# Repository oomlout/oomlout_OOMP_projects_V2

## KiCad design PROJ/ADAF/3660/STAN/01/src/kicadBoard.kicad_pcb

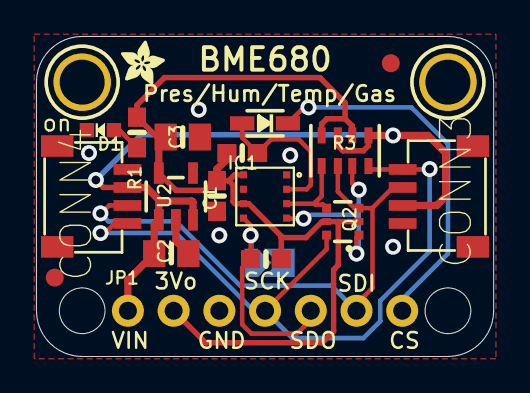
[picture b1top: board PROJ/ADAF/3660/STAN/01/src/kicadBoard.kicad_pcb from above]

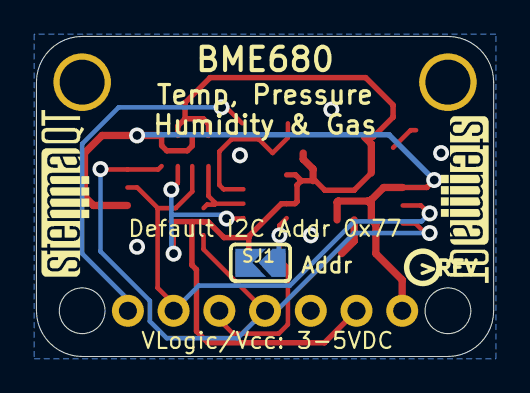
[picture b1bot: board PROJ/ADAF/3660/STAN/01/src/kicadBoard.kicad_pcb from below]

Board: 2 copper layers, 25.4 x 17.8 mm, 26 parts (4 on the bottom side), 11 nets.

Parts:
@HOLE0, @HOLE1: (no value)
C1: 0.1uF; 0603-NO
C2, C3: 10uF; 0805-NO
CONN3, CONN4: STEMMA_I2C_QT; JST_SH4
D1: GREEN; CHIPLED_0603_NOOUTLINE
D2: 1N4148; SOD-323
FID3, FID4: FIDUCIAL_1MM
IC1: BME680
JP1: 1X07_ROUND_70
Q2: BSS138; SOT363
R1, R4, R5: 10K; 0603-NO
R3: 10K; RESPACK_4X0603
SJ1: SOLDERJUMPER_ARROW_NOPASTE
U2: AP2112K-3.3; SOT23-5
U$1, U$17: MOUNTINGHOLE2.5; MOUNTINGHOLE_2.5_PLATED
U$4: ADAFRUIT_2.5MM
U$25: PCBFEAT-REV-040
U$30, U$31: STEMMAQT

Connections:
3.3V: C1.1, C3.1, IC1.6, IC1.8, JP1.2, Q2.2, Q2.5, R1.1, R3.2, R3.4, R4.2, R5.2, U2.5
CS: D2.C, JP1.7
CS_3V: D2.A, IC1.2, R5.1
GND: C1.2, C2.2, C3.2, CONN3.1, CONN4.1, D1.C, IC1.1, IC1.7, JP1.3, SJ1.2, U2.2
unnamed: D1.A, R1.2
SCK/SCL: CONN3.4, CONN4.4, JP1.4, Q2.6, R3.8
SCK_3V: IC1.4, Q2.1, R3.7
SDI/SDA: CONN3.3, CONN4.3, JP1.6, Q2.3, R3.6
SDI_3V: IC1.3, Q2.4, R3.5
SDO/ADR: IC1.5, JP1.5, R4.1, SJ1.1
VCC: C2.1, CONN3.2, CONN4.2, JP1.1, R3.1, R3.3, U2.1, U2.3

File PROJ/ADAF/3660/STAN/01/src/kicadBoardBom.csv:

"Id";"Designator";"Package";"Quantity";"Designation";"Supplier and ref";
1;"R5,R1,R4";"0603-NO";3;"10K";;;
2;"@HOLE1,@HOLE0";"";2;"";;;
3;"U$1,U$17";"MOUNTINGHOLE_2.5_PLATED";2;"MOUNTINGHOLE2.5";;;
4;"C2,C3";"0805-NO";2;"10uF";;;
5;"Q2";"SOT363";1;"BSS138";;;
6;"R3";"RESPACK_4X0603";1;"10K";;;
7;"C1";"0603-NO";1;"0.1uF";;;
8;"U2";"SOT23-5";1;"AP2112K-3.3";;;
9;"D1";"CHIPLED_0603_NOOUTLINE";1;"GREEN";;;
10;"U$4";"ADAFRUIT_2.5MM";1;"";;;
11;"CONN3,CONN4";"JST_SH4";2;"STEMMA_I2C_QT";;;
12;"D2";"SOD-323";1;"1N4148";;;
13;"IC1";"BME680";1;"BME680";;;
14;"JP1";"1X07_ROUND_70";1;"";;;
15;"FID3,FID4";"FIDUCIAL_1MM";2;"FIDUCIAL_1MM";;;
16;"U$25";"PCBFEAT-REV-040";1;"";;;
17;"U$31,U$30";"STEMMAQT";2;"";;;
18;"SJ1";"SOLDERJUMPER_ARROW_NOPASTE";1;"";;;

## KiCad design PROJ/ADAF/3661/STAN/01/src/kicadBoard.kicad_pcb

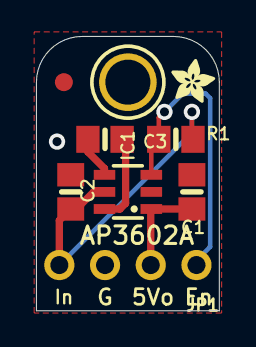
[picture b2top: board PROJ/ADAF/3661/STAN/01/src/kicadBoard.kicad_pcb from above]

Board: 2 copper layers, 10.2 x 15.2 mm, 10 parts (1 on the bottom side), 6 nets.

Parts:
C1, C2: 10uF; 0805-NO
C3: 1uF; 0805-NO
FID1: FIDUCIAL""; FIDUCIAL_1MM
IC1: AP3602; SOT23-6
JP1: 1X04_ROUND
R1: 100K; 0805-NO
U$9: MOUNTINGHOLE2.5; MOUNTINGHOLE_2.5_PLATED
U$10: PCBFEAT-REV-040
U$11: ADAFRUIT_2.5MM

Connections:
5.0V: C1.1, IC1.1, JP1.2
GND: C1.2, C2.2, IC1.2, JP1.3
unnamed: C3.2, IC1.6
unnamed: C3.1, IC1.4
VIN: C2.1, IC1.5, JP1.4, R1.1
~SHDN: IC1.3, JP1.1, R1.2

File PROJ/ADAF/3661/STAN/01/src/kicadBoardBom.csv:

"Id";"Designator";"Package";"Quantity";"Designation";"Supplier and ref";
1;"C2,C1";"0805-NO";2;"10uF";;;
2;"FID1";"FIDUCIAL_1MM";1;"FIDUCIAL""";;;
3;"U$11";"ADAFRUIT_2.5MM";1;"";;;
4;"U$9";"MOUNTINGHOLE_2.5_PLATED";1;"MOUNTINGHOLE2.5";;;
5;"JP1";"1X04_ROUND";1;"";;;
6;"R1";"0805-NO";1;"100K";;;
7;"IC1";"SOT23-6";1;"AP3602";;;
8;"C3";"0805-NO";1;"1uF";;;
9;"U$10";"PCBFEAT-REV-040";1;"";;;

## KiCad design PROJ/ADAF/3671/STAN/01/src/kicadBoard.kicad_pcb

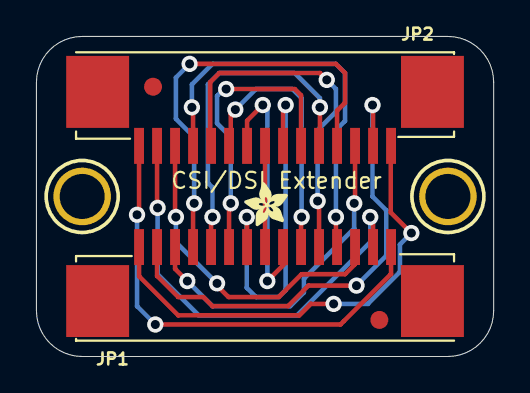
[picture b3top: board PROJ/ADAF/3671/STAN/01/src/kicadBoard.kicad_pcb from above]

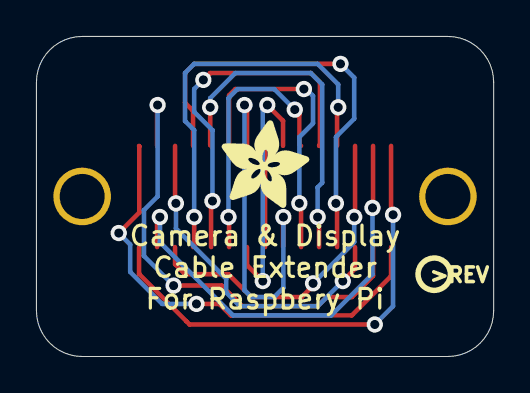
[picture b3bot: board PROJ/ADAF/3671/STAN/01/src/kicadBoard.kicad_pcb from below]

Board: 2 copper layers, 25.4 x 17.8 mm, 9 parts (2 on the bottom side), 15 nets.

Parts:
FID1, FID2: FIDUCIAL_1MM
JP1, JP2: FPC_15PIN_1.0MM
U$2, U$3: MOUNTINGHOLE2.5; MOUNTINGHOLE_2.5_PLATED
U$4: ADAFRUIT_2.5MM
U$5: ADAFRUIT_5MM
U$6: PCBFEAT-REV-040

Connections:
unnamed: JP1.1, JP2.1
unnamed: JP1.2, JP2.2
unnamed: JP1.3, JP2.3
unnamed: JP1.4, JP2.4
unnamed: JP1.5, JP2.5
unnamed: JP1.6, JP2.6
unnamed: JP1.7, JP2.7
unnamed: JP1.8, JP2.8
unnamed: JP1.9, JP2.9
unnamed: JP1.10, JP2.10
unnamed: JP1.11, JP2.11
unnamed: JP1.12, JP2.12
unnamed: JP1.13, JP2.13
unnamed: JP1.14, JP2.14
unnamed: JP1.15, JP2.15

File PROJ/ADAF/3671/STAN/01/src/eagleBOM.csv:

"Part";"Value";"Device";"Package";"Description";"BOM";
"FID1";"FIDUCIAL_1MM";"FIDUCIAL_1MM";"FIDUCIAL_1MM";"Fiducial Alignment Points";"EXCLUDE";
"FID2";"FIDUCIAL_1MM";"FIDUCIAL_1MM";"FIDUCIAL_1MM";"Fiducial Alignment Points";"EXCLUDE";
"JP1";"";"HEADER-1X15_FPC1MM_PI";"FPC_15PIN_1.0MM";"1x15 Header";"";
"JP2";"";"HEADER-1X15_FPC1MM_PI";"FPC_15PIN_1.0MM";"1x15 Header";"";
"U$2";"MOUNTINGHOLE2.5";"MOUNTINGHOLE2.5";"MOUNTINGHOLE_2.5_PLATED";"Mounting Hole";"EXCLUDE";
"U$3";"MOUNTINGHOLE2.5";"MOUNTINGHOLE2.5";"MOUNTINGHOLE_2.5_PLATED";"Mounting Hole";"EXCLUDE";

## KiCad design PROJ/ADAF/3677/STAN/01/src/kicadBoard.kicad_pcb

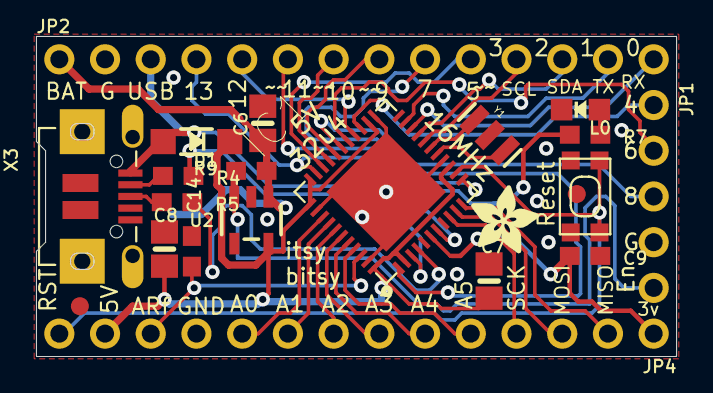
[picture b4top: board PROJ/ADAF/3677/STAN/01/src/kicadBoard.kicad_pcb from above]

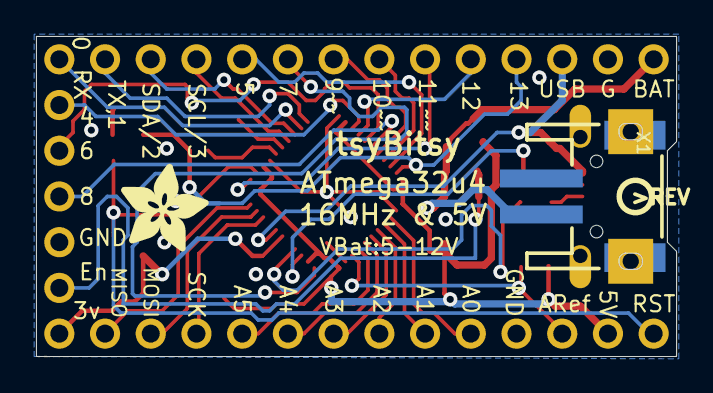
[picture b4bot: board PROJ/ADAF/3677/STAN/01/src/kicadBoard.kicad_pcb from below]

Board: 2 copper layers, 35.6 x 17.8 mm, 25 parts (3 on the bottom side), 38 nets.

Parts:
C6, C8: 10µF; 0805-NO
C7: 10uF; 0805-NO
C9, C14: 1uF; 0603-NO
D1: MBR120; SOD-123
IC1: ATMEGA32U4-MU; TQFN44_7MM
JP1: 1X05_ROUND
JP2, JP4: 1X14_ROUND70
L0: RED; CHIPLED_0805_NOOUTLINE
R4, R5: 22; 0603-NO
R7: 2.2K; 0603-NO
R9: 100k; 0603-NO
SW1: SPST_TACT-KMR2; KMR2
U2: MIC5225-5.0; SOT23-5
U$4: ADAFRUIT_5MM
U$7: ADAFRUIT_3.5MM
U$10: PCBFEAT-REV-040
U$34, U$35: FIDUCIAL""; FIDUCIAL_1MM
X1: JSTPH2
X3: microUSB; 4UCONN_20329_V2
Y1: 16MHz; RESONATOR-SMD

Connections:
3.3V: C9.1, IC1.6, JP4.1
+5V: C7.1, C8.1, D1.C, IC1.2, IC1.14, IC1.24, IC1.33, IC1.34, IC1.44, JP4.13, U2.5
A0: IC1.36, JP4.10
A1: IC1.37, JP4.9
A2: IC1.38, JP4.8
A3: IC1.39, JP4.7
A4: IC1.40, JP4.6
A5: IC1.41, JP4.5
AREF: C14.1, IC1.42, JP4.12
D0: IC1.20, JP2.14
D1: IC1.21, JP2.13
D4: IC1.25, JP1.1
D5: IC1.31, JP2.10
D6: IC1.27, JP1.2
D7: IC1.1, JP2.9
D8: IC1.28, JP1.3
D9: IC1.29, JP2.8
D10: IC1.30, JP2.7
D11: IC1.12, JP2.6
D12: IC1.26, JP2.5
D13: IC1.32, JP2.4, R7.1
D+: IC1.4, R5.2
D-: IC1.3, R4.2
EN: JP1.5, R9.2, U2.3
GND: C6.2, C7.2, C8.2, C9.2, C14.2, IC1.5, IC1.15, IC1.23, IC1.35, IC1.43, JP1.4, JP2.2, JP4.11, L0.C, SW1.2, SW1.4, U2.2, X1.1, X3.BASE@1, X3.BASE@2, X3.GND, X3.SPRT@1, X3.SPRT@2, X3.SPRT@3, X3.SPRT@4, Y1.2
MISO: IC1.11, JP4.2
MOSI: IC1.10, JP4.3
unnamed: L0.A, R7.2
unnamed: IC1.16, Y1.3
unnamed: IC1.17, Y1.1
unnamed: R5.1, X3.D+
unnamed: R4.1, X3.D-
RST: IC1.13, JP4.14, SW1.1, SW1.3
SCK: IC1.9, JP4.4
SCL: IC1.18, JP2.11
SDA: IC1.19, JP2.12
VBAT: C6.1, JP2.1, R9.1, U2.1, X1.2
VBUS: D1.A, IC1.7, JP2.3, X3.VBUS

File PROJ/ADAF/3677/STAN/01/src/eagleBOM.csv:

"Part";"Value";"Device";"Package";"Description";"BOM";
"C6";"10µF";"CAP_CERAMIC0805-NOOUTLINE";"0805-NO";"Ceramic Capacitors";"";
"C7";"10uF";"CAP_CERAMIC0805-NOOUTLINE";"0805-NO";"Ceramic Capacitors";"";
"C8";"10µF";"CAP_CERAMIC0805-NOOUTLINE";"0805-NO";"Ceramic Capacitors";"";
"C9";"1uF";"CAP_CERAMIC0603_NO";"0603-NO";"Ceramic Capacitors";"";
"C14";"1uF";"CAP_CERAMIC0603_NO";"0603-NO";"Ceramic Capacitors";"";
"D1";"MBR120";"DIODE-SCHOTTKYSOD-123";"SOD-123";"";"";
"IC1";"ATMEGA32U4-MU";"ATMEGA32U4-MU";"TQFN44_7MM";"http://www.ladyada.net/library/eagle";"";
"JP1";"";"HEADER-1X5ROUND";"1X05_ROUND";"PIN HEADER";"";
"JP2";"";"HEADER-1X14";"1X14_ROUND70";"";"";
"JP4";"";"HEADER-1X14";"1X14_ROUND70";"";"";
"L";"RED";"LED0805_NOOUTLINE";"CHIPLED_0805_NOOUTLINE";"LED";"";
"R4";"22";"RESISTOR_0603_NOOUT";"0603-NO";"Resistors";"";
"R5";"22";"RESISTOR_0603_NOOUT";"0603-NO";"Resistors";"";
"R7";"2.2K";"RESISTOR_0603_NOOUT";"0603-NO";"Resistors";"";
"R9";"100k";"RESISTOR_0603_NOOUT";"0603-NO";"Resistors";"";
"SW1";"SPST_TACT-KMR2";"SPST_TACT-KMR2";"KMR2";"SMT 6mm switch, EVQQ2 series";"";
"U$34";"FIDUCIAL""";"FIDUCIAL""";"FIDUCIAL_1MM";"Fiducial Alignment Points";"EXCLUDE";
"U$35";"FIDUCIAL""";"FIDUCIAL""";"FIDUCIAL_1MM";"Fiducial Alignment Points";"EXCLUDE";
"U2";"MIC5225-5.0";"VREG_SOT23-5";"SOT23-5";"SOT23-5 Fixed Voltage Regulators";"";
"X1";"";"CON_JST_PH_2PIN";"JSTPH2";"JST 2-Pin Right-Angle Connector";"";
"X3";"microUSB";"USB_MICRO_20329_V2";"4UCONN_20329_V2";"USB Connectors";"";
"Y1";"16MHz";"RESONATORSMD";"RESONATOR-SMD";"Resonator";"";

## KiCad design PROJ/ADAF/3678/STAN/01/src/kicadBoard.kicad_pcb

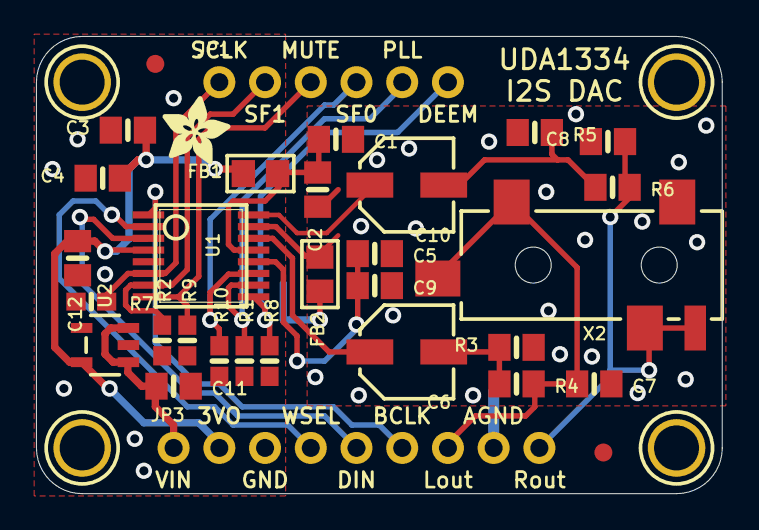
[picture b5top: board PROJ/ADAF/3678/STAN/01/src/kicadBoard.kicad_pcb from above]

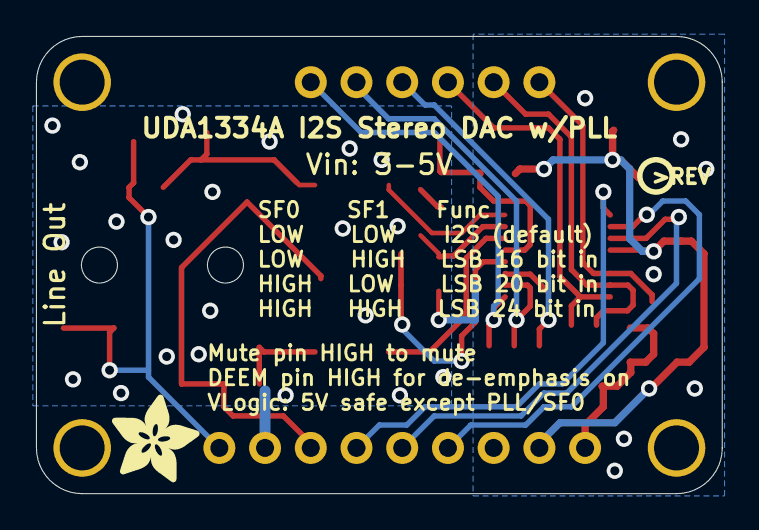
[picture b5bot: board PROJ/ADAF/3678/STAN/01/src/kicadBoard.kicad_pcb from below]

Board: 2 copper layers, 38.1 x 25.4 mm, 38 parts (2 on the bottom side), 21 nets.

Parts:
C1, C3, C9: 0.1uF; 0805-NO
C2, C4, C5, C11, C12: 10uF; 0805-NO
C6, C10: 47uF; PANASONIC_C
C7, C8: 0.01uF; 0805-NO
FB1, FB2: Ferrite; 0805
FID1, FID2: FIDUCIAL_1MM
JP1: 1X06_ROUND_70
JP3: 1X09_ROUND_70
R1, R2, R7, R8, R9, R10: 10k; 0603-NO
R3, R5: 220k; 0805-NO
R4, R6: 100; 0805-NO
U1: UDA1334ATS; SSOP16_4.4MM
U2: MIC5225-3.3; SOT23-5
U$5: PCBFEAT-REV-040
U$6: ADAFRUIT_5MM
U$11, U$12, U$13, U$14: MOUNTINGHOLE2.5; MOUNTINGHOLE_2.5_PLATED
U$29: ADAFRUIT_3.5MM
X2: 19269; 4UCONN_19269

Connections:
3.3V: C3.1, C4.1, C12.1, FB1.2, JP3.2, U1.4, U2.5
AGND: C1.2, C2.2, C5.2, C7.2, C8.2, C9.2, FB2.1, JP3.8, R3.1, R5.1, U1.15, X2.1
BITCLK_IN: JP3.6, U1.1
DATA_IN: JP3.5, U1.3
DEEM/CLKOUT: JP1.6, R8.2, U1.9
GND: C3.2, C4.2, C11.2, C12.2, FB2.2, JP3.3, R1.1, R2.1, R7.1, R8.1, R9.1, R10.1, U1.5, U2.2
MUTE: JP1.3, R9.2, U1.8
unnamed: C5.1, C9.1, U1.12
unnamed: C1.1, C2.1, FB1.1, U1.13
unnamed: C10.+, U1.16
unnamed: C6.+, U1.14
unnamed: C6.-, R3.2, R4.1
unnamed: C10.-, R5.2, R6.1
OUTL: C7.1, JP3.7, R4.2, X2.2, X2.4
OUTR: C8.1, JP3.9, R6.2, X2.3, X2.5
PLL_IN: JP1.5, R1.2, U1.10
SFOR0: JP1.4, R10.2, U1.11
SFOR1: JP1.2, R2.2, U1.7
SYSCLK_IN: JP1.1, R7.2, U1.6
VIN: C11.1, JP3.1, U2.1, U2.3
WORDSEL_IN: JP3.4, U1.2

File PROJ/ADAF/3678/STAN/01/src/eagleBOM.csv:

"Part";"Value";"Device";"Package";"Description";"BOM";
"C1";"0.1uF";"CAP_CERAMIC0805-NOOUTLINE";"0805-NO";"Ceramic Capacitors";"";
"C2";"10uF";"CAP_CERAMIC0805-NOOUTLINE";"0805-NO";"Ceramic Capacitors";"";
"C3";"0.1uF";"CAP_CERAMIC0805-NOOUTLINE";"0805-NO";"Ceramic Capacitors";"";
"C4";"10uF";"CAP_CERAMIC0805-NOOUTLINE";"0805-NO";"Ceramic Capacitors";"";
"C5";"10uF";"CAP_CERAMIC0805-NOOUTLINE";"0805-NO";"Ceramic Capacitors";"";
"C6";"47uF";"CAP_ELECTROLYTICPANASONIC_C";"PANASONIC_C";"Electrolytic Capacitors";"";
"C7";"0.01uF";"CAP_CERAMIC0805-NOOUTLINE";"0805-NO";"Ceramic Capacitors";"";
"C8";"0.01uF";"CAP_CERAMIC0805-NOOUTLINE";"0805-NO";"Ceramic Capacitors";"";
"C9";"0.1uF";"CAP_CERAMIC0805-NOOUTLINE";"0805-NO";"Ceramic Capacitors";"";
"C10";"47uF";"CAP_ELECTROLYTICPANASONIC_C";"PANASONIC_C";"Electrolytic Capacitors";"";
"C11";"10uF";"CAP_CERAMIC0805-NOOUTLINE";"0805-NO";"Ceramic Capacitors";"";
"C12";"10uF";"CAP_CERAMIC0805-NOOUTLINE";"0805-NO";"Ceramic Capacitors";"";
"FB1";"Ferrite";"FERRITE0805";"0805";"Ferrite Bead";"";
"FB2";"Ferrite";"FERRITE0805";"0805";"Ferrite Bead";"";
"FID1";"FIDUCIAL_1MM";"FIDUCIAL_1MM";"FIDUCIAL_1MM";"Fiducial Alignment Points";"EXCLUDE";
"FID2";"FIDUCIAL_1MM";"FIDUCIAL_1MM";"FIDUCIAL_1MM";"Fiducial Alignment Points";"EXCLUDE";
"JP1";"";"HEADER-1X670MIL";"1X06_ROUND_70";"PIN HEADER";"";
"JP3";"";"HEADER-1X970MIL";"1X09_ROUND_70";"PIN HEADER";"";
"R1";"10k";"RESISTOR_0603_NOOUT";"0603-NO";"Resistors";"";
"R2";"10k";"RESISTOR_0603_NOOUT";"0603-NO";"Resistors";"";
"R3";"220k";"RESISTOR0805_NOOUTLINE";"0805-NO";"Resistors";"";
"R4";"100";"RESISTOR0805_NOOUTLINE";"0805-NO";"Resistors";"";
"R5";"220k";"RESISTOR0805_NOOUTLINE";"0805-NO";"Resistors";"";
"R6";"100";"RESISTOR0805_NOOUTLINE";"0805-NO";"Resistors";"";
"R7";"10k";"RESISTOR_0603_NOOUT";"0603-NO";"Resistors";"";
"R8";"10k";"RESISTOR_0603_NOOUT";"0603-NO";"Resistors";"";
"R9";"10k";"RESISTOR_0603_NOOUT";"0603-NO";"Resistors";"";
"R10";"10k";"RESISTOR_0603_NOOUT";"0603-NO";"Resistors";"";
"U$11";"MOUNTINGHOLE2.5";"MOUNTINGHOLE2.5";"MOUNTINGHOLE_2.5_PLATED";"Mounting Hole";"EXCLUDE";
"U$12";"MOUNTINGHOLE2.5";"MOUNTINGHOLE2.5";"MOUNTINGHOLE_2.5_PLATED";"Mounting Hole";"EXCLUDE";
"U$13";"MOUNTINGHOLE2.5";"MOUNTINGHOLE2.5";"MOUNTINGHOLE_2.5_PLATED";"Mounting Hole";"EXCLUDE";
"U$14";"MOUNTINGHOLE2.5";"MOUNTINGHOLE2.5";"MOUNTINGHOLE_2.5_PLATED";"Mounting Hole";"EXCLUDE";
"U1";"UDA1334ATS";"AUDIO_I2S_UDA1334""";"SSOP16_4.4MM";"UDA1334 I2C Audio DAC";"";
"U2";"MIC5225-3.3";"VREG_SOT23-5";"SOT23-5";"SOT23-5 Fixed Voltage Regulators";"";
"X2";"19269";"AUDIO_3.5MMJACK";"4UCONN_19269";"3.5MM Audio Jack";"";

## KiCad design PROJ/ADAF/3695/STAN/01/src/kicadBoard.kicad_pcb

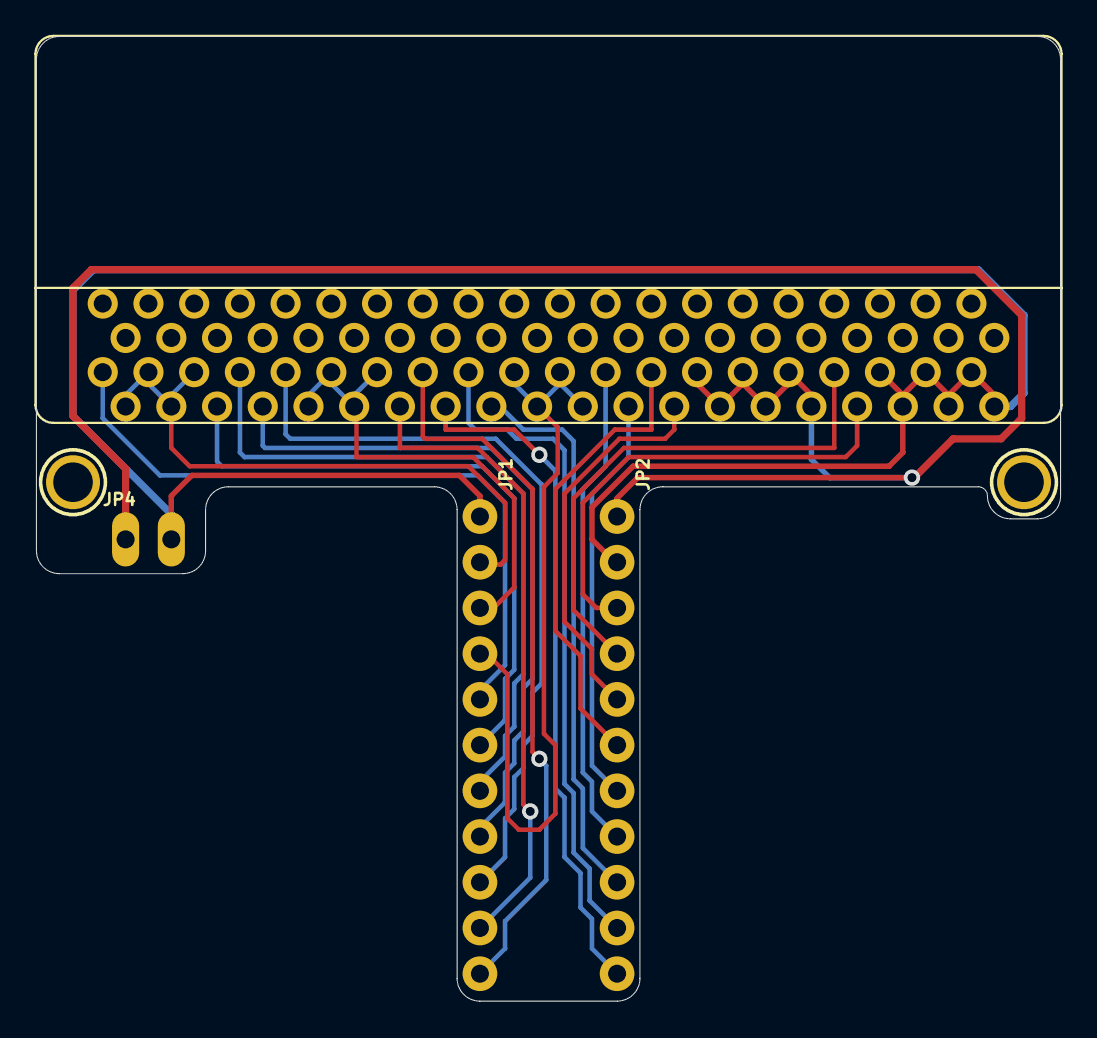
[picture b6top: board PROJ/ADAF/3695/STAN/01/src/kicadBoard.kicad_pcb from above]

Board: 2 copper layers, 56.9 x 53.6 mm, 8 parts (1 on the bottom side), 21 nets.

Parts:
JP1, JP2: 1X11_ROUND_76
JP4: 1X02_OVAL
MB1: MICRO:BIT_RA; 2X20_CARDEDGE_RA
U$3: TBREADBIT_BOT
U$6: TBREADBIT_TOP
U$9, U$10: MOUNTINGHOLE2.0; MOUNTINGHOLE_2.0_PLATED

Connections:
3.3V: JP2.1, JP4.1, MB1.27, MB1.28, MB1.29, MB1.30, MB1.31, MB1.32
GND: JP1.1, JP2.2, JP4.2, MB1.35, MB1.36, MB1.37, MB1.38, MB1.39, MB1.40
P0: JP1.2, MB1.2, MB1.3, MB1.4, MB1.5
P1: JP1.3, MB1.10, MB1.11, MB1.12, MB1.13
P2: JP1.4, MB1.19, MB1.20, MB1.21, MB1.22
P3: JP1.5, MB1.1
P4: JP1.6, MB1.6
P5: JP1.7, MB1.7
P6: JP1.8, MB1.8
P7: JP1.9, MB1.9
P8: JP1.10, MB1.14
P9: JP1.11, MB1.15
P10: JP2.11, MB1.16
P11: JP2.10, MB1.17
P12: JP2.9, MB1.18
P13: JP2.8, MB1.23
P14: JP2.7, MB1.24
P15: JP2.6, MB1.25
P16: JP2.5, MB1.26
SCL: JP2.4, MB1.33
SDA: JP2.3, MB1.34

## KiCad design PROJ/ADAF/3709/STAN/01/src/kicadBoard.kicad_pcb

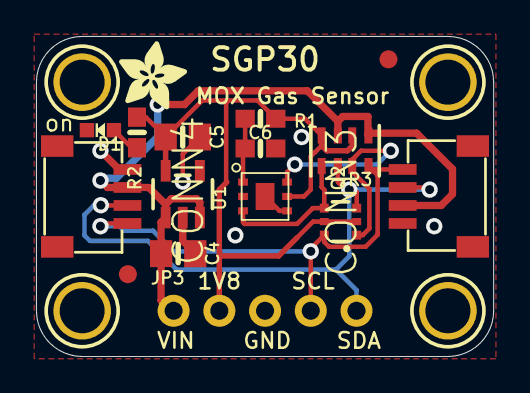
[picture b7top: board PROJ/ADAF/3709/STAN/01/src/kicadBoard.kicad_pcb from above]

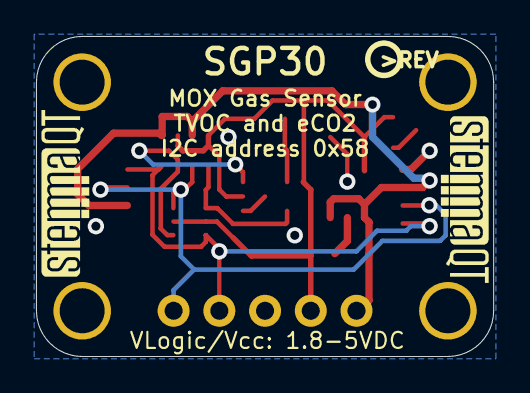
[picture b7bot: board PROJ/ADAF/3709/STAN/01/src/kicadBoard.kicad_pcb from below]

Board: 2 copper layers, 25.4 x 17.8 mm, 23 parts (3 on the bottom side), 9 nets.

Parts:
C4, C5: 10uF; 0805-NO
C6: 0.1uF; 0603-NO
CONN3, CONN4: STEMMA_I2C_QT; JST_SH4
D1: RED; CHIPLED_0603_NOOUTLINE
FID3, FID4: FIDUCIAL_1MM
JP3: 1X05_ROUND_70
Q2: BSS138; SOT363
R1: 4.7ohm; 0603-NO
R2: 10K; 0603-NO
R3: 10K; RESPACK_4X0603
U1: MCP-1.8V; SOT23-5
U$28, U$29, U$31, U$32: MOUNTINGHOLE2.5; MOUNTINGHOLE_2.5_PLATED
U$34: ADAFRUIT_3.5MM
U$35: PCBFEAT-REV-040
U$36, U$37: STEMMAQT
X1: SGP30

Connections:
3.3V: C5.1, JP3.2, Q2.2, Q2.5, R1.2, R2.1, R3.2, R3.4, U1.5, X1.5
GND: C4.2, C5.2, C6.2, CONN3.1, CONN3.MT1, CONN3.MT2, CONN4.1, CONN4.MT1, CONN4.MT2, D1.C, JP3.3, U1.2, X1.2, X1.4, X1.P$7
unnamed: D1.A, R2.2
SCL: CONN3.4, CONN4.4, JP3.4, Q2.6, R3.8
SCL_LV: Q2.1, R3.7, X1.6
SDA: CONN3.3, CONN4.3, JP3.5, Q2.3, R3.6
SDA_LV: Q2.4, R3.5, X1.3
SENSOR_VDD: C6.1, R1.1, X1.1
VCC: C4.1, CONN3.2, CONN4.2, JP3.1, R3.1, R3.3, U1.1, U1.3

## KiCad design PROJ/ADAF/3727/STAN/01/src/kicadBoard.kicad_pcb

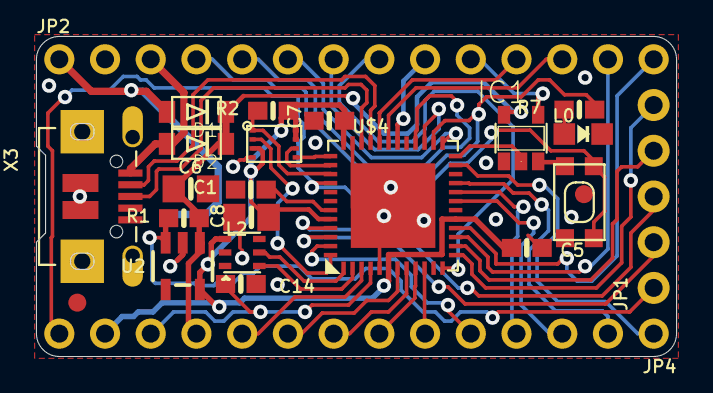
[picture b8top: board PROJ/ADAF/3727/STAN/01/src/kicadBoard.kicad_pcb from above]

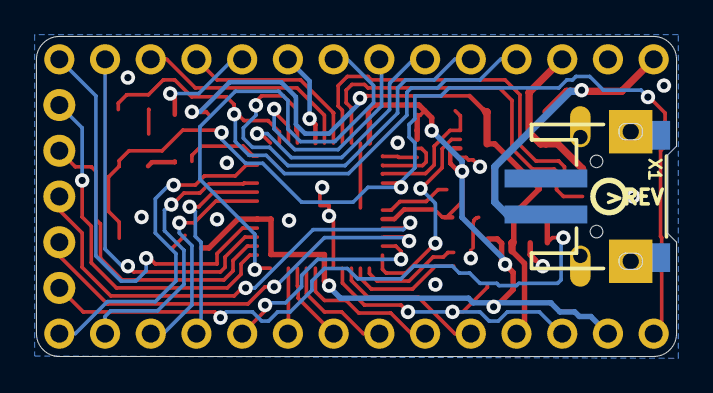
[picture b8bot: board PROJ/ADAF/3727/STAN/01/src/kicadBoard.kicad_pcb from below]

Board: 2 copper layers, 35.6 x 17.8 mm, 28 parts (3 on the bottom side), 44 nets.

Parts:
C1, C5, C7, C14: 1uF; 0603-NO
C6, C8: 10µF; 0805-NO
D1, D2: MBR120; SOD-123FL
IC1: 74HCT1G125; SOT23-5
JP1: 1X05_ROUND_70
JP2, JP4: 1X14_ROUND70
L0: RED; CHIPLED_0805_NOOUTLINE
L2: AP102-2020; APA102_2020
R1, R2: 100k; 0603-NO
R7: 2.2K; 0603-NO
SW1: SPST_TACT-KMR2; KMR2
U1: flash; USON8
U2: AP2112K-3.3; SOT23-5
U$4: ATSAMD21G18; TQFN48_7MM
U$13: PCBFEAT-REV-040
U$14: ITSYM0_TOP
U$15: ITSYM0_BOT
U$34, U$35: FIDUCIAL_1MM
X1: JSTPH2
X3: microUSB; 4UCONN_20329_V2

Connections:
+3V3: C5.1, C7.1, C8.1, JP4.13, L2.3, R2.1, U1.3, U1.7, U1.8, U2.5, U$4.6, U$4.17, U$4.36, U$4.44
A0: JP4.10, U$4.3
A1: JP4.9, U$4.7
A2: JP4.8, U$4.8
A3: JP4.7, U$4.9
A4: JP4.6, U$4.10
A5: JP4.5, U$4.47
AREF: C14.1, JP4.12, U$4.4
D0: JP2.14, U$4.16
D1: JP2.13, U$4.15
D2: JP4.1, U$4.23
D3: JP1.4, U$4.14
D4: JP1.5, U$4.13
D5: IC1.2, U$4.24
D5_5V: IC1.4, JP2.10
D7: JP2.9, U$4.30
D9: JP2.8, U$4.12
D10: JP2.7, U$4.27
D11: JP2.6, U$4.25
D12: JP2.5, U$4.28
D13: JP2.4, R7.1, U$4.26
D+: U$4.34, X3.D+
D-: U$4.33, X3.D-
EN: JP1.1, R1.2, U2.3
FLASH_CS: R2.2, U1.1, U$4.39
FLASH_MISO: U1.2, U$4.48
FLASH_MOSI: U1.5, U$4.37
FLASH_SCK: U1.6, U$4.38
GND: C1.2, C5.2, C6.2, C7.2, C8.2, C14.2, IC1.1, IC1.3, JP2.2, L0.C, L2.4, SW1.2, SW1.4, U1.4, U2.2, U$4.5, U$4.18, U$4.35, U$4.42, U$4.THERMAL, X1.1, X3.BASE@1, X3.BASE@2, X3.GND, X3.SPRT@1, X3.SPRT@2, X3.SPRT@3, X3.SPRT@4
MISO: JP4.2, U$4.21
MOSI: JP4.3, U$4.19
unnamed: L2.5, U$4.1
unnamed: L0.A, R7.2
unnamed: L2.6, U$4.2
SCK: JP4.4, U$4.20
SCL: JP2.11, U$4.32
SDA: JP2.12, U$4.31
SWCLK: JP1.3, U$4.45
SWDIO: JP1.2, U$4.46
VBAT: D1.A, JP2.1, X1.2
VBUS: D2.A, JP2.3, X3.VBUS
VDDCORE: C1.1, U$4.43
VHI: C6.1, D1.C, D2.C, IC1.5, JP4.11, R1.1, U2.1
~RESET: JP4.14, SW1.1, SW1.3, U$4.40
